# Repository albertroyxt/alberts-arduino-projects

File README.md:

# alberts-projects
you are free to use my files

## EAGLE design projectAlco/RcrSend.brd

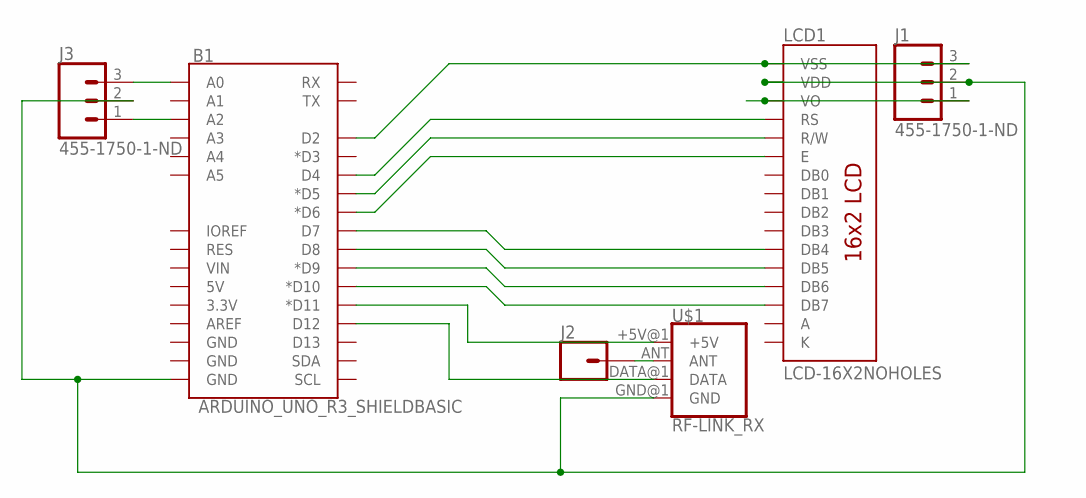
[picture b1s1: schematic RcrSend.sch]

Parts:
B1: ARDUINO_UNO_R3_SHIELDBASIC; UNO_R3_SHIELD
J1, J3: 455-1750-1-ND; 1X03
J2: CONN_01; 1X01
LCD1: LCD-16X2NOHOLES; LCD-16X2_NOHOLESNOSILK
U$1: RF-LINK_RX

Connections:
A: LCD1.15 (A)
K: LCD1.16 (K)
unnamed: B1.D2, J1.3, LCD1.1 (VSS)
unnamed: B1.GND@0 (GND), J1.2, J3.2, LCD1.2 (VDD), U$1.GND@1 (GND)
unnamed: B1.D4, LCD1.4 (RS)
unnamed: B1.D5 (*D5), LCD1.5 (R/W)
unnamed: B1.D6 (*D6), LCD1.6 (E)
unnamed: B1.D7, LCD1.11 (DB4)
unnamed: B1.D8, LCD1.12 (DB5)
unnamed: B1.D9 (*D9), LCD1.13 (DB6)
unnamed: B1.D10 (*D10), LCD1.14 (DB7)
unnamed: J2.1, U$1.ANT
unnamed: B1.D11 (*D11), U$1.+5V@1 (+5V)
unnamed: B1.D12, U$1.DATA@1 (DATA)
unnamed: B1.A2, J3.1
unnamed: J1.1, LCD1.3 (VO)
unnamed: B1.A0, J3.3

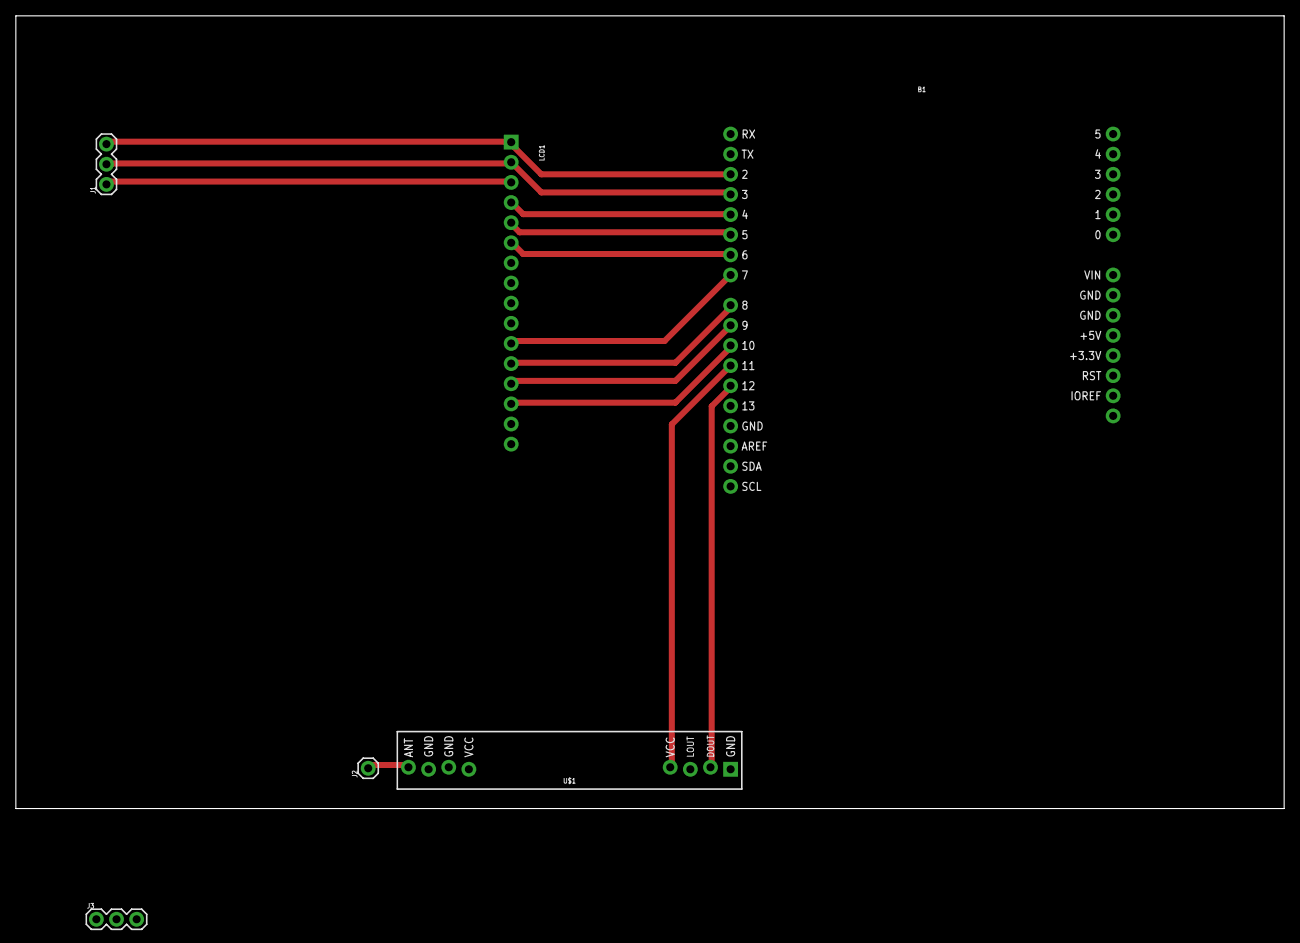
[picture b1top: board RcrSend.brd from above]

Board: 2 copper layers, 160.0 x 100.0 mm, 6 parts (0 on the bottom side), 15 nets.

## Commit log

2019-04-09 Add files via upload
    place stylesheet on a folder named css

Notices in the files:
parts and their libraries:
SparkFun-Boards: Licensing: Creative Commons ShareAlike 4.0 International - https://creativecommons.org/licenses/by-sa/4.0
